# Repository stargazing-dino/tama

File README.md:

# nineapt

## Build & flash

```sh
cargo run --release
```

If you hit `APPROTECT` errors:

```sh
probe-rs erase --chip nRF54L15 --allow-erase-all
```

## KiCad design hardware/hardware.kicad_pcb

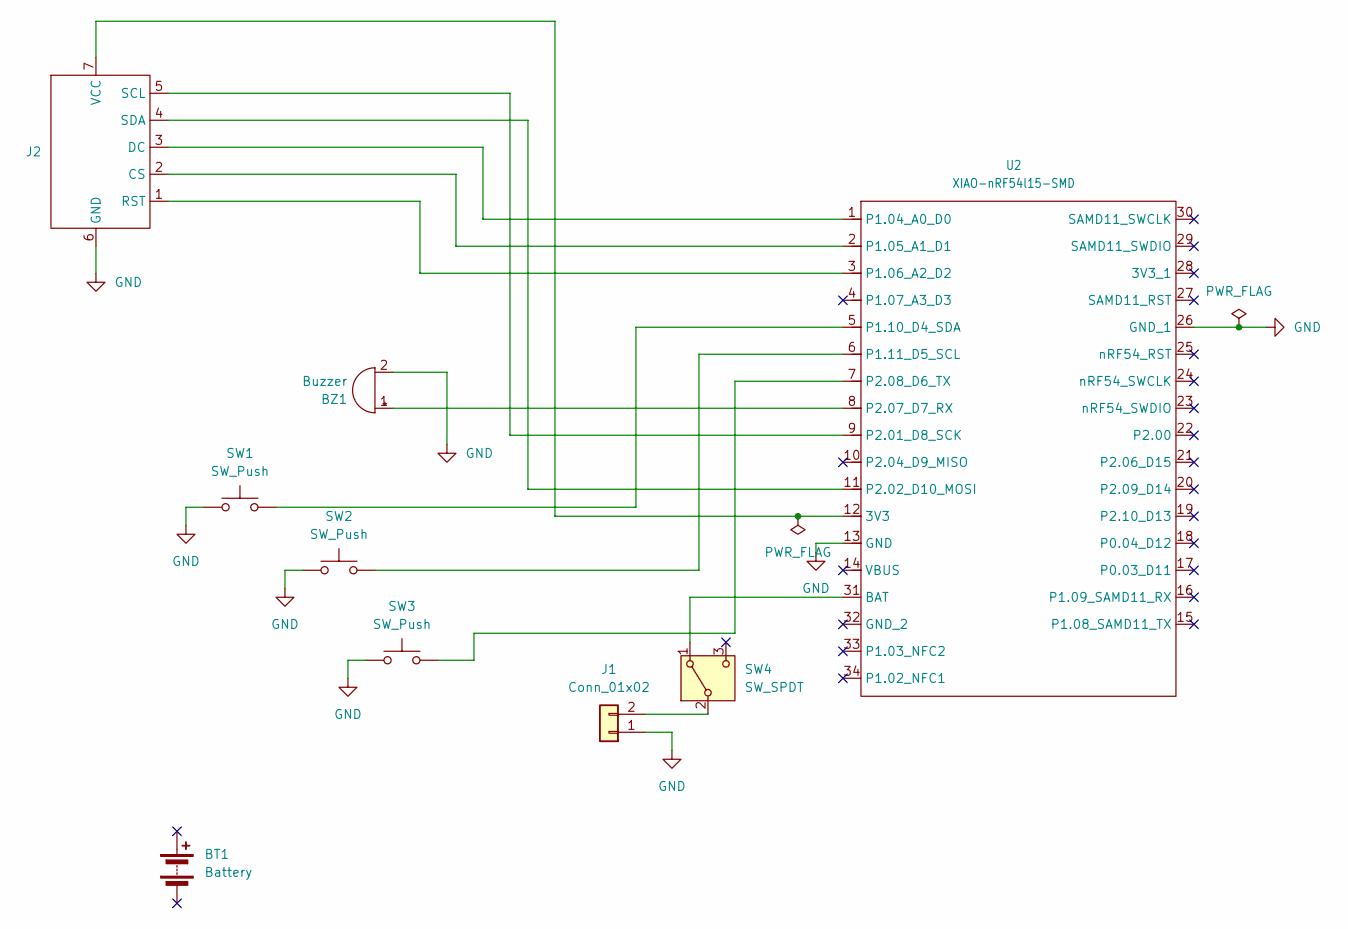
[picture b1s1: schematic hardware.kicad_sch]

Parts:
BT1: Battery
BZ1: Buzzer; Buzzer_TDK_PS1240P02BT_D12.2mm_H6.5mm
J1: Conn_01x02; JST_PH_S2B-PH-SM4-TB_1x02-1MP_P2.00mm_Horizontal
J2: GC9A01_1.28in_Module
SW1, SW2, SW3: SW_Push; SW_Push_1P1T_NO_CK_PTS125Sx43SMTR
SW4: SW_SPDT; SW_Slide-03_Wuerth-WS-SLTV_10x2.5x6.4_P2.54mm
U2: XIAO-nRF54l15-SMD

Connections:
GND: BZ1.2 (-), J1.1, J2.6 (GND), SW1.1, SW2.1, SW3.1, U2.13 (GND), U2.26 (GND_1)
unnamed: BZ1.1 (+), U2.8 (P2.07_D7_RX)
unnamed: J1.2, SW4.2 (B)
unnamed: J2.2 (CS), U2.2 (P1.05_A1_D1)
unnamed: J2.3 (DC), U2.1 (P1.04_A0_D0)
unnamed: J2.1 (RST), U2.3 (P1.06_A2_D2)
unnamed: J2.5 (SCL), U2.9 (P2.01_D8_SCK)
unnamed: J2.4 (SDA), U2.11 (P2.02_D10_MOSI)
unnamed: J2.7 (VCC), U2.12 (3V3)
unnamed: SW4.1 (A), U2.31 (BAT)
unnamed: SW1.2, U2.5 (P1.10_D4_SDA)
unnamed: SW2.2, U2.6 (P1.11_D5_SCL)
unnamed: SW3.2, U2.7 (P2.08_D6_TX)

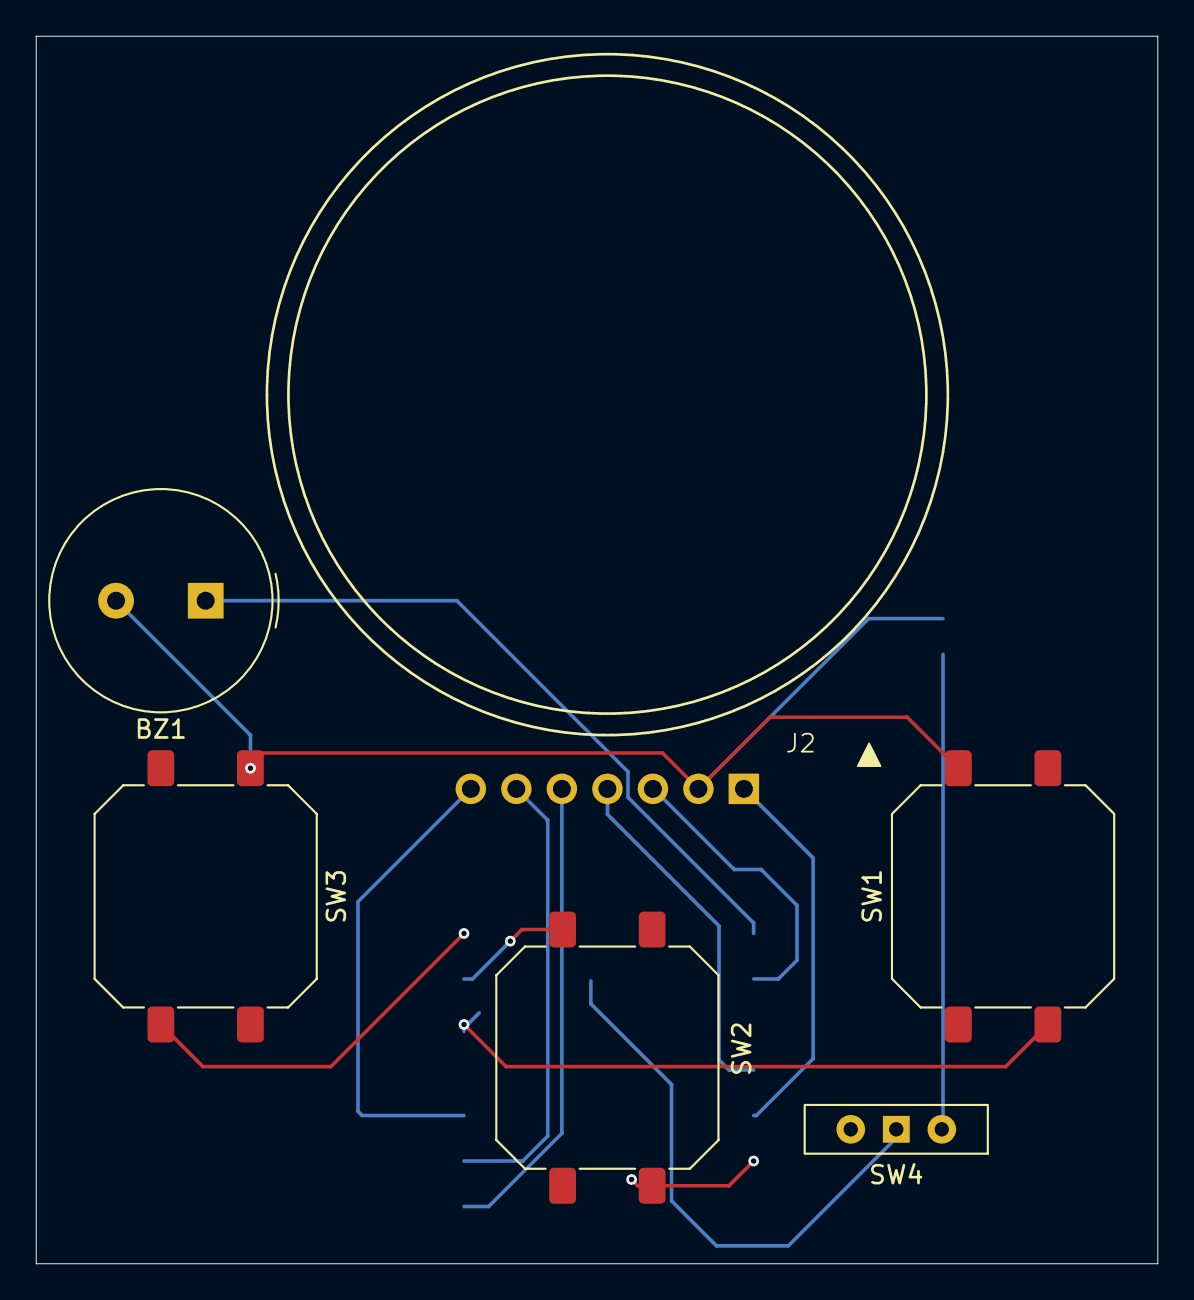
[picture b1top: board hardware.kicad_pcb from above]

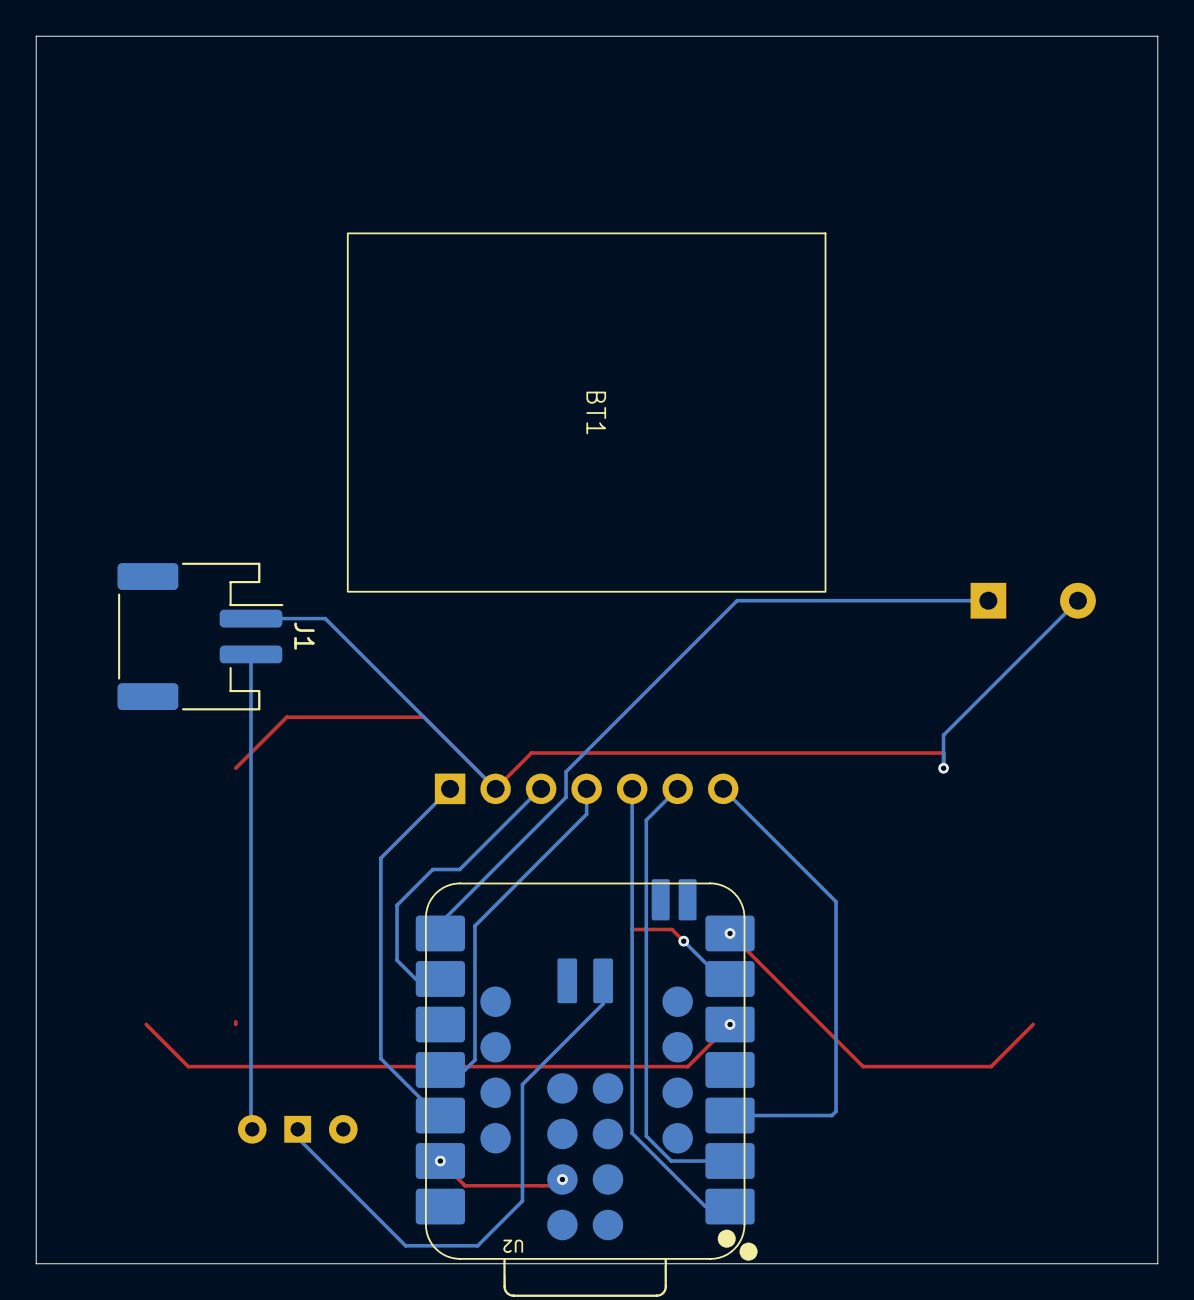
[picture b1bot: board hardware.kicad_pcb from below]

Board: 2 copper layers, 62.6 x 68.5 mm, 9 parts (3 on the bottom side), 13 nets.

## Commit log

2026-04-27 Initial commit: XIAO nRF54L15 blinky scaffold
2026-04-27 Add GC9A01 driver hitting SPI bus floor (~31 fps full-frame)
2026-04-27 Add minimal README and XIAO pin reference image
2026-04-30 Add KiCad hardware project and ignore KiCad cruft
2026-04-30 Add GC9A01 1.28in display dimension reference
2026-04-30 Move XIAO pinout into hardware/datasheets and rename
2026-04-30 Define PCB stackup and bump trace width to 0.381mm
2026-05-04 Bring up GC9A01 with animated cat and idle state machine
2026-05-05 Add tiled wallpaper background behind cat
2026-05-05 Wire D4/D5/D6 buttons to feed, pet, play actions
2026-05-06 Add three-room world with camera, walking cat, and event-driven inputs
2026-05-07 Rename game module to cat; relocate Button to input and rendering to world
2026-05-07 Map buttons to cat actions in main; cat consumes intent, not hardware
2026-05-07 Split build.rs into encode/cat/themes/props modules; extract bedroom prop sheet
2026-05-07 Furnish bedroom, kitchen, and bath; add prop layout tools
2026-05-07 Use high bit of rng for cat walk direction to remove rightward bias
2026-05-07 Hoist blit clipping out of inner loop and run render flat-out for ~2.7x fps
2026-05-07 Remove info and comment
2026-05-11 Rename crate to nineapt
2026-05-11 Replace remaining tama references in code and docs
2026-05-11 Emit pixel data as include_bytes! bin files instead of hex literals
2026-05-11 Remove tools/ — preview moved to nineapt-py pygame port
2026-05-11 Derive framebuffer W/H from GC9A01::FRAMEBUFFER_SIZE
2026-05-11 Reorganize into firmware/, kicad/, pygame/ top-level folders
2026-05-11 Add emote sprite sheet pipeline + asset attributions
2026-05-11 Keep itch/ and DayOff/ as visible placeholders with setup READMEs
2026-05-12 Move cat sprite sheet to /elthen-cats and gitignore — license forbids redistribution
